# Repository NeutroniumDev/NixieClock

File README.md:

# NixieClock
  NOTE: this is not a completed project. The code is incomplete, and therefor the hardware has not been fully tested. DON'T BUILD THIS YET, OR ASSUME RISKS. 

  A clock consisting of 6 nixie tubes, controlled by 3 high voltage shift registers. It differs from most other nixie clocks in that every segment of every nixie tube can be turned on, as opposed to one number per tube. This enables more complex animations. The 3 high voltage shift registers also, theoretically (not implemented) support controlling more than 6 nixie tubes because of leftover pins. The clock uses an ESP32-C3 to enable synchronizing the time with NTP, and it also acts as the microcontroller. Finally, the clock technically has an RTC chip, although in retrospect it's sorta unnecessary (and not implemented in code lmao).

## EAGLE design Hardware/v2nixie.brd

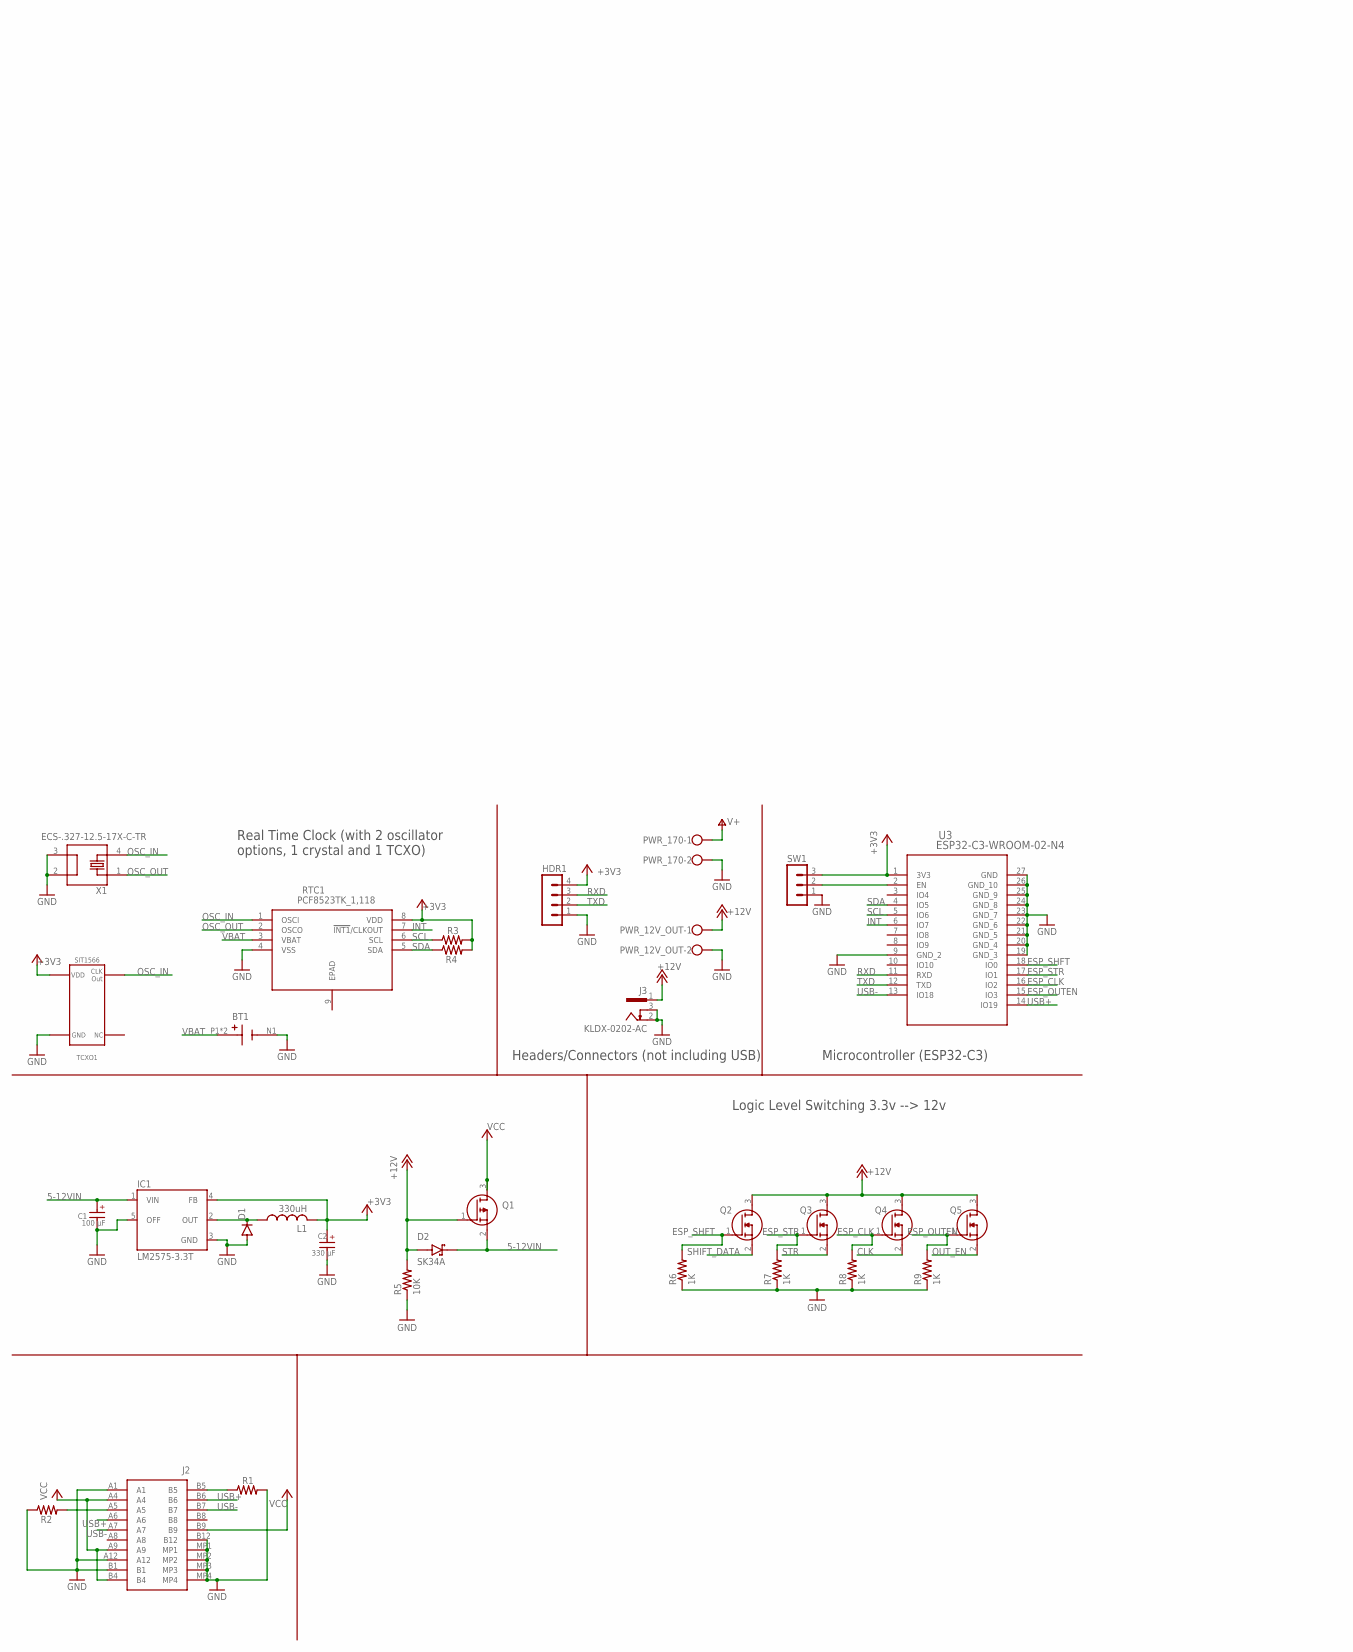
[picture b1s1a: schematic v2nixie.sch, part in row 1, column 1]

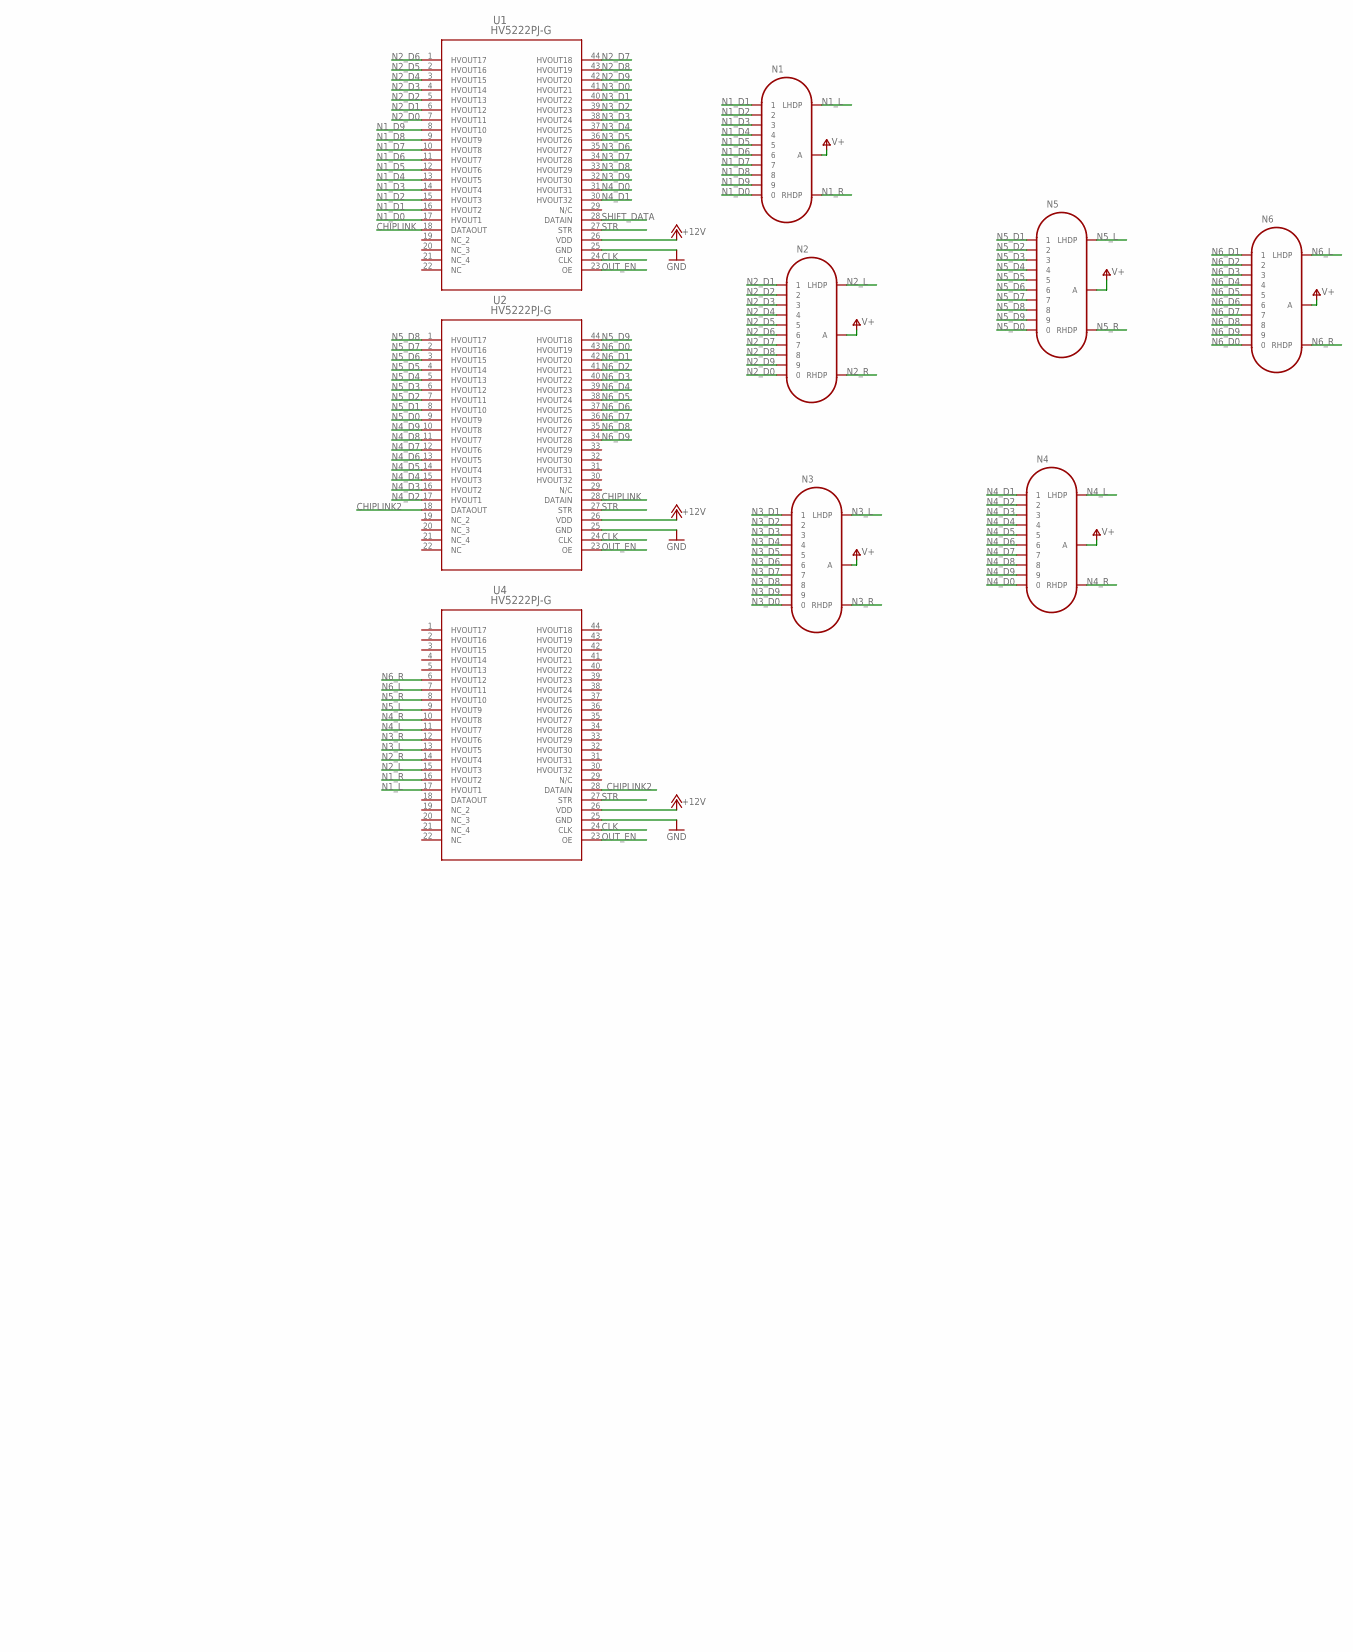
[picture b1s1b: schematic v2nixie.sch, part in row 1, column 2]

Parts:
BT1: BAT-HLD-001-TR; BAT_BAT-HLD-001-TR
C1: 100 µF; WCAP-PTG5_8X11.5(DXL)
C2: 330 µF; WCAP-PTG5_8X8(DXL)
D1: DIODE-DO201-15; DO201-15
D2: SK34A; DIOM4325X250N
HDR1: MA04-1
IC1: LM2575-3.3T; TO220-5
J2: USB4110-GF-A; USB4110GFA
J3: KLDX-0202-AC; KYCON_KLDX-0202-AC
L1: 330uH; 6000-XXXX-RC
N1, N2, N3, N4, N5, N6: IN-14
PWR_12V_OUT, PWR_170: W237-102
Q1: SSM3J117TU,LF_T; SSM3J117TULFT
Q2, Q3, Q4, Q5: RU1J002YNTCL; SOTFL65P210X105-3N
R1, R2: 5.1K; R0805
R3, R4: 10K; R0805
R5: 10K; M0805
R6, R7, R8, R9: 1K; M0805
RTC1: PCF8523TK_1,118; SON80P400X400X100-9N
SW1: MA03-1
TCXO1: SIT1566
U1, U2, U4: HV5222PJ-G; PLCC44_MC_MCH
U3: ESP32-C3-WROOM-02-N4; IC18_ESP32-C3-WROOM-02-N4_EXP
X1: ECS-.327-12.5-17X-C-TR; XTAL_ECS-.327-12.5-17X-C-TR

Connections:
5-12VIN: C1.1 (+), D2.C (K), IC1.1 (VIN), Q1.2 (S)
+3V3: C2.1 (+), HDR1.4, IC1.4 (FB), L1.2, R3.2, R4.2, RTC1.8 (VDD), SW1.3, TCXO1.VDD, U3.1 (3V3)
+12V: D2.A, J3.1, PWR_12V_OUT.1, Q1.1 (G), Q2.3 (D), Q3.3 (D), Q4.3 (D), Q5.3 (D), R5.2, U1.26 (VDD), U2.26 (VDD), U4.26 (VDD)
CHIPLINK: U1.18 (DATAOUT), U2.28 (DATAIN)
CHIPLINK2: U2.18 (DATAOUT), U4.28 (DATAIN)
CLK: Q4.2 (S), U1.24 (CLK), U2.24 (CLK), U4.24 (CLK)
ESP_CLK: Q4.1 (G), R8.2, U3.16 (IO2)
ESP_OUTEN: Q5.1 (G), R9.2, U3.15 (IO3)
ESP_SHFT: Q2.1 (G), R6.2, U3.18 (IO0)
ESP_STR: Q3.1 (G), R7.2, U3.17 (IO1)
GND: BT1.N1 (-), C1.2 (-), C2.2 (-), D1.A, HDR1.1, IC1.3 (GND), IC1.5 (OFF), J2.A1, J2.A12, J2.B1, J2.B12, J2.MP1, J2.MP2, J2.MP3, J2.MP4, J3.2, J3.3, PWR_12V_OUT.2, PWR_170.2, R1.2, R2.1, R5.1, R6.1, R7.1, R8.1, R9.1, RTC1.4 (VSS), SW1.1, TCXO1.GND, U1.25 (GND), U2.25 (GND), U3.9 (GND_2), U3.19 (GND_3), U3.20 (GND_4), U3.21 (GND_5), U3.22 (GND_6), U3.23 (GND_7), U3.24 (GND_8), U3.25 (GND_9), U3.26 (GND_10), U3.27 (GND), U4.25 (GND), X1.2, X1.3
INT: RTC1.7 (!INT1!/CLKOUT), U3.6 (IO7)
N1_D0: N1.0, U1.17 (HVOUT1)
N1_D1: N1.1, U1.16 (HVOUT2)
N1_D2: N1.2, U1.15 (HVOUT3)
N1_D3: N1.3, U1.14 (HVOUT4)
N1_D4: N1.4, U1.13 (HVOUT5)
N1_D5: N1.5, U1.12 (HVOUT6)
N1_D6: N1.6, U1.11 (HVOUT7)
N1_D7: N1.7, U1.10 (HVOUT8)
N1_D8: N1.8, U1.9 (HVOUT9)
N1_D9: N1.9, U1.8 (HVOUT10)
N1_L: N1.LHDP, U4.17 (HVOUT1)
N1_R: N1.RHDP, U4.16 (HVOUT2)
N2_D0: N2.0, U1.7 (HVOUT11)
N2_D1: N2.1, U1.6 (HVOUT12)
N2_D2: N2.2, U1.5 (HVOUT13)
N2_D3: N2.3, U1.4 (HVOUT14)
N2_D4: N2.4, U1.3 (HVOUT15)
N2_D5: N2.5, U1.2 (HVOUT16)
N2_D6: N2.6, U1.1 (HVOUT17)
N2_D7: N2.7, U1.44 (HVOUT18)
N2_D8: N2.8, U1.43 (HVOUT19)
N2_D9: N2.9, U1.42 (HVOUT20)
N2_L: N2.LHDP, U4.15 (HVOUT3)
N2_R: N2.RHDP, U4.14 (HVOUT4)
N3_D0: N3.0, U1.41 (HVOUT21)
N3_D1: N3.1, U1.40 (HVOUT22)
N3_D2: N3.2, U1.39 (HVOUT23)
N3_D3: N3.3, U1.38 (HVOUT24)
N3_D4: N3.4, U1.37 (HVOUT25)
N3_D5: N3.5, U1.36 (HVOUT26)
N3_D6: N3.6, U1.35 (HVOUT27)
N3_D7: N3.7, U1.34 (HVOUT28)
N3_D8: N3.8, U1.33 (HVOUT29)
N3_D9: N3.9, U1.32 (HVOUT30)
N3_L: N3.LHDP, U4.13 (HVOUT5)
N3_R: N3.RHDP, U4.12 (HVOUT6)
N4_D0: N4.0, U1.31 (HVOUT31)
N4_D1: N4.1, U1.30 (HVOUT32)
N4_D2: N4.2, U2.17 (HVOUT1)
N4_D3: N4.3, U2.16 (HVOUT2)
N4_D4: N4.4, U2.15 (HVOUT3)
N4_D5: N4.5, U2.14 (HVOUT4)
N4_D6: N4.6, U2.13 (HVOUT5)
N4_D7: N4.7, U2.12 (HVOUT6)
N4_D8: N4.8, U2.11 (HVOUT7)
N4_D9: N4.9, U2.10 (HVOUT8)
N4_L: N4.LHDP, U4.11 (HVOUT7)
N4_R: N4.RHDP, U4.10 (HVOUT8)
N5_D0: N5.0, U2.9 (HVOUT9)
N5_D1: N5.1, U2.8 (HVOUT10)
N5_D2: N5.2, U2.7 (HVOUT11)
N5_D3: N5.3, U2.6 (HVOUT12)
N5_D4: N5.4, U2.5 (HVOUT13)
N5_D5: N5.5, U2.4 (HVOUT14)
N5_D6: N5.6, U2.3 (HVOUT15)
N5_D7: N5.7, U2.2 (HVOUT16)
N5_D8: N5.8, U2.1 (HVOUT17)
N5_D9: N5.9, U2.44 (HVOUT18)
N5_L: N5.LHDP, U4.9 (HVOUT9)
N5_R: N5.RHDP, U4.8 (HVOUT10)
N6_D0: N6.0, U2.43 (HVOUT19)
N6_D1: N6.1, U2.42 (HVOUT20)
N6_D2: N6.2, U2.41 (HVOUT21)
N6_D3: N6.3, U2.40 (HVOUT22)
N6_D4: N6.4, U2.39 (HVOUT23)
N6_D5: N6.5, U2.38 (HVOUT24)
N6_D6: N6.6, U2.37 (HVOUT25)
N6_D7: N6.7, U2.36 (HVOUT26)
N6_D8: N6.8, U2.35 (HVOUT27)
N6_D9: N6.9, U2.34 (HVOUT28)
N6_L: N6.LHDP, U4.7 (HVOUT11)
N6_R: N6.RHDP, U4.6 (HVOUT12)
unnamed: J2.A5, R2.2
unnamed: SW1.2, U3.2 (EN)
unnamed: J2.B5, R1.1
unnamed: D1.C, IC1.2 (OUT), L1.1
OSC_IN: RTC1.1 (OSCI), TCXO1.CLK_OUT, X1.4
OSC_OUT: RTC1.2 (OSCO), X1.1
OUT_EN: Q5.2 (S), U1.23 (OE), U2.23 (OE), U4.23 (OE)
RXD: HDR1.3, U3.11 (RXD)
SCL: R3.1, RTC1.6 (SCL), U3.5 (IO6)
SDA: R4.1, RTC1.5 (SDA), U3.4 (IO5)
SHIFT_DATA: Q2.2 (S), U1.28 (DATAIN)
STR: Q3.2 (S), U1.27 (STR), U2.27 (STR), U4.27 (STR)
TXD: HDR1.2, U3.12 (TXD)
USB+: J2.A6, J2.B6, U3.14 (IO19)
USB-: J2.A7, J2.B7, U3.13 (IO18)
V+: N1.A, N2.A, N3.A, N4.A, N5.A, N6.A, PWR_170.1
VBAT: BT1.P1 (+), BT1.P2 (+), RTC1.3 (VBAT)
VCC: J2.A4, J2.A9, J2.B4, J2.B9, Q1.3 (D)

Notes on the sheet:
Real Time Clock (with 2 oscillator options, 1 crystal and 1 TCXO)
Headers/Connectors (not including USB)
Microcontroller (ESP32-C3)
Logic Level Switching 3.3v --> 12v

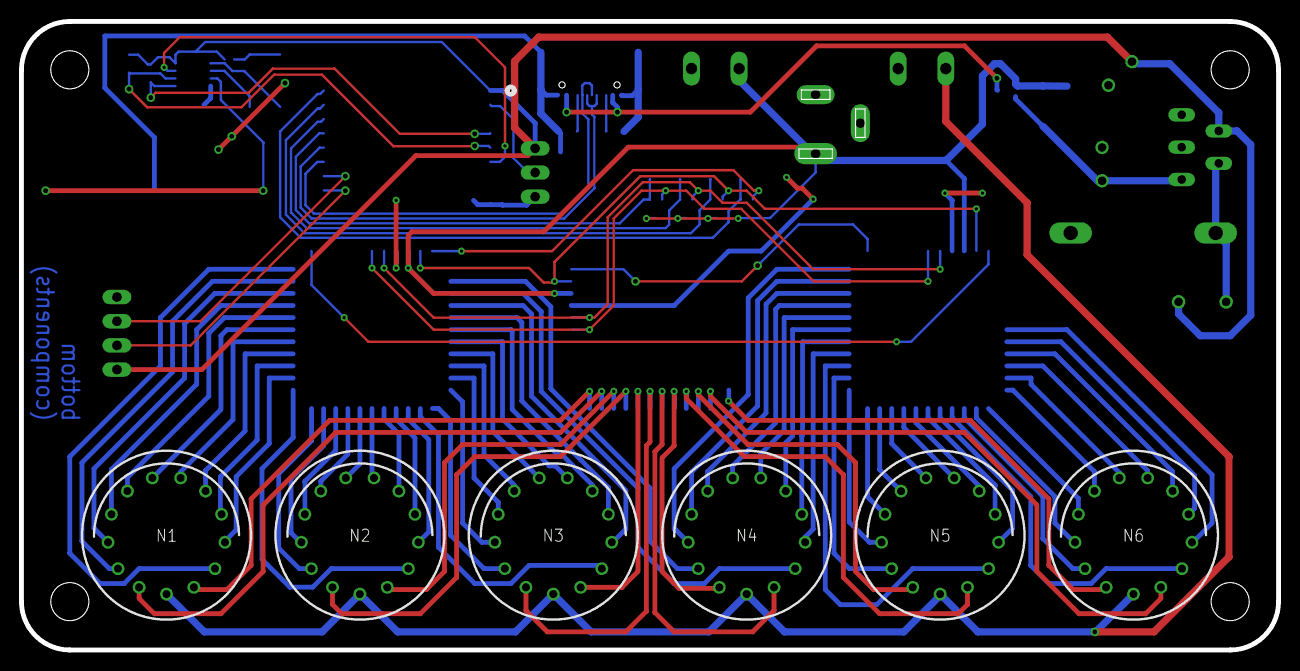
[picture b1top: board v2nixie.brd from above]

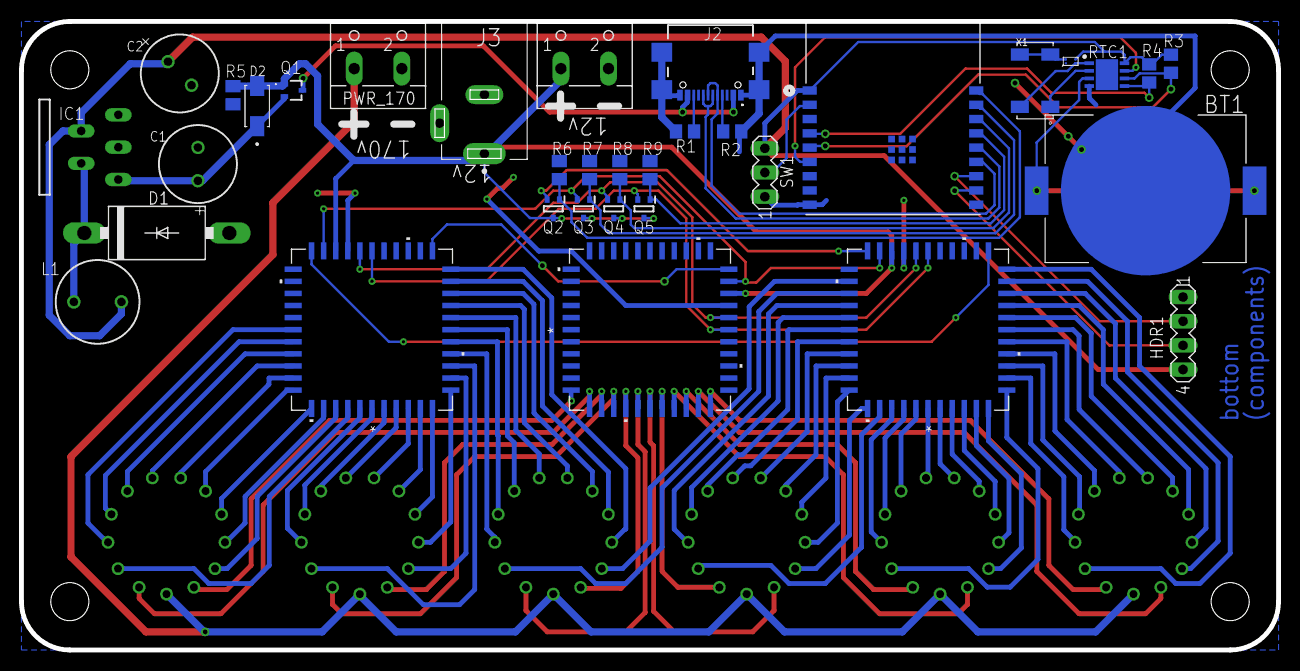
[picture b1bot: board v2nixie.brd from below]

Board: 2 copper layers, 132.1 x 66.0 mm, 40 parts (34 on the bottom side), 102 nets.

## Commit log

2022-08-15 eeeee
2022-08-15 added some comments

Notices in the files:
parts and their libraries:
Wurth_Capacitors_WCAP-PTG5: Copyright: Würth Elektronik
COPYRIGHT: Copyright (C) 2022 Ultra Librarian. All rights reserved.
